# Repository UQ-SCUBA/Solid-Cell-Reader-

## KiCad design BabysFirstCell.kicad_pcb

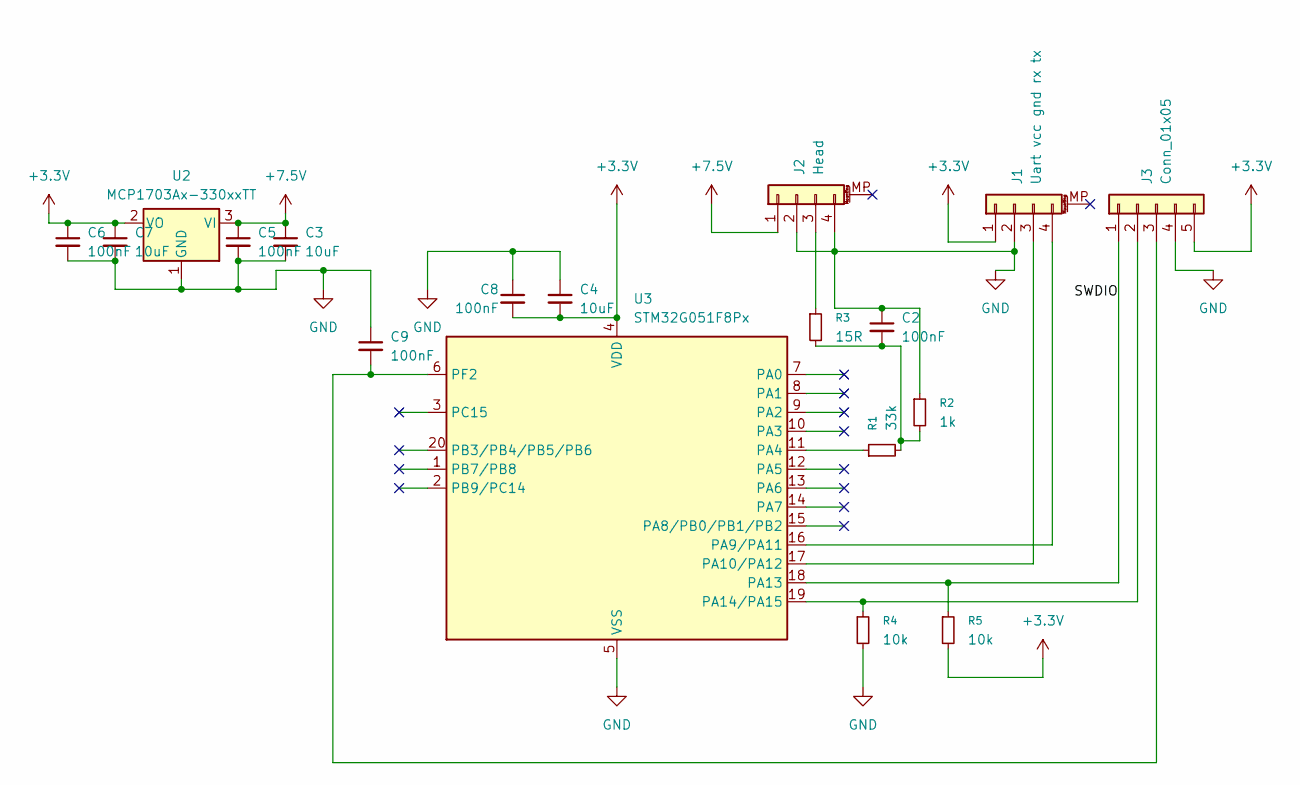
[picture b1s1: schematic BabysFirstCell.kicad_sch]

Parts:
C2, C5, C8, C9: 100nF; C_01005_0402Metric
C3, C4: 10uF; C_01005_0402Metric
C6: 100nF; R_0603_1608Metric
C7: 10uF; C_0201_0603Metric
J1: Uart vcc gnd rx tx; Molex_DuraClik_502352-0400_1x04-1MP_P2.00mm_Vertical
J2: Head; JST_PH_B4B-PH-K_1x04_P2.00mm_Vertical
J3: Conn_01x05; Molex_KK-396_A-41791-0005_1x05_P3.96mm_Vertical
R1: 33k; R_01005_0402Metric
R2: 1k; R_01005_0402Metric
R3: 15R; R_01005_0402Metric
R4, R5: 10k; R_01005_0402Metric
U2: MCP1703Ax-330xxTT; SOT-23
U3: STM32G051F8Px; TSSOP-20_4.4x6.5mm_P0.65mm

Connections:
+3.3V: C4.2, C6.1, C7.1, C8.2, J1.1, J3.5, R5.2, U2.2 (VO), U3.4 (VDD)
+7.5V: C3.1, C5.1, J2.1, U2.3 (VI)
/SWDIO: J3.1, R5.1, U3.18 (PA13)
GND: C2.1, C3.2, C4.1, C5.2, C6.2, C7.2, C8.1, C9.1, J1.2, J2.2, J2.4, J3.4, R2.1, R4.2, U2.1 (GND), U3.5 (VSS)
unnamed: C2.2, R1.2, R2.2, R3.2
unnamed: J1.3, U3.17 (PA10/PA12)
unnamed: J1.4, U3.16 (PA9/PA11)
unnamed: J2.3, R3.1
unnamed: J3.2, R4.1, U3.19 (PA14/PA15)
unnamed: C9.2, J3.3, U3.6 (PF2)
unnamed: R1.1, U3.11 (PA4)

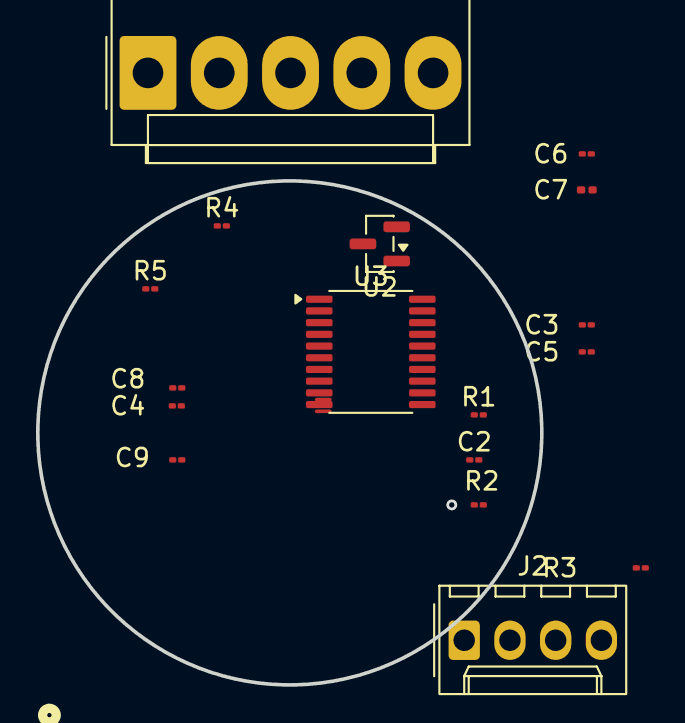
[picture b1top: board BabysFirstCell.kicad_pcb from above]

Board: 4 copper layers, 28.0 x 28.0 mm, 18 parts (1 on the bottom side), 11 nets.

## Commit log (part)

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2026-03-27 Initial KiCad project upload
2026-03-29 Add EasyEDA Pro project files
2026-03-29 Fixed Mistakes
